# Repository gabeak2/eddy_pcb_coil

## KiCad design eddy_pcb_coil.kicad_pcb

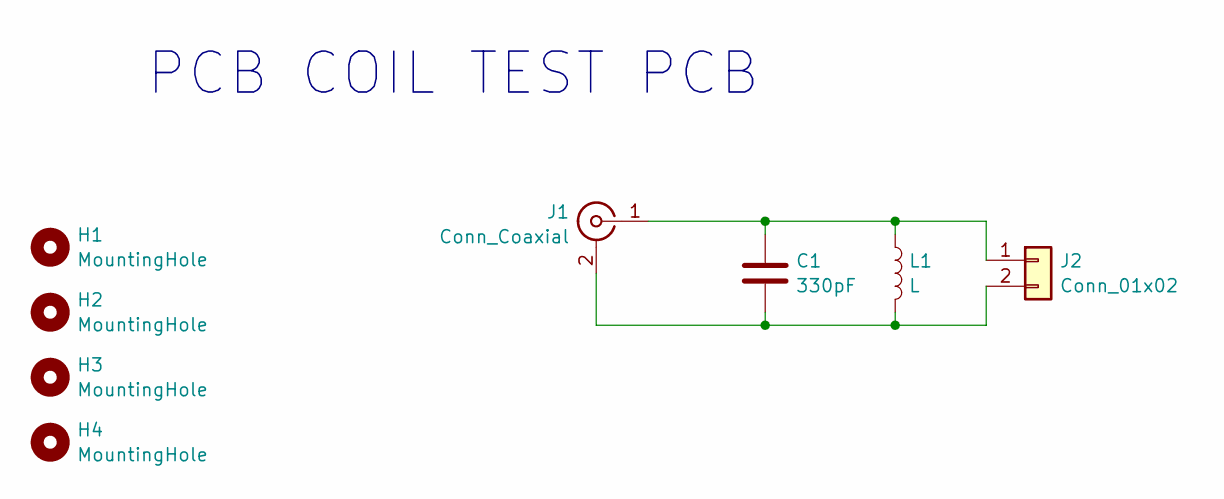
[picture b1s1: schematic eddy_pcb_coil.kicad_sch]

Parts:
C1: 330pF; C_0805_2012Metric; LCSC C527075
H1, H2, H3, H4: MountingHole; MountingHole_3.2mm_M3
J1: Conn_Coaxial; SMB_Jack_Vertical; LCSC C2797251
J2: Conn_01x02; PinHeader_1x02_P2.54mm_Vertical
L1: L; pcb_coil_30_turns_2_layers_30mm_od

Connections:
unnamed: C1.2, J1.2 (Ext), J2.2, L1.2
unnamed: C1.1, J1.1 (In), J2.1, L1.1

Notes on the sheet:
PCB COIL TEST PCB

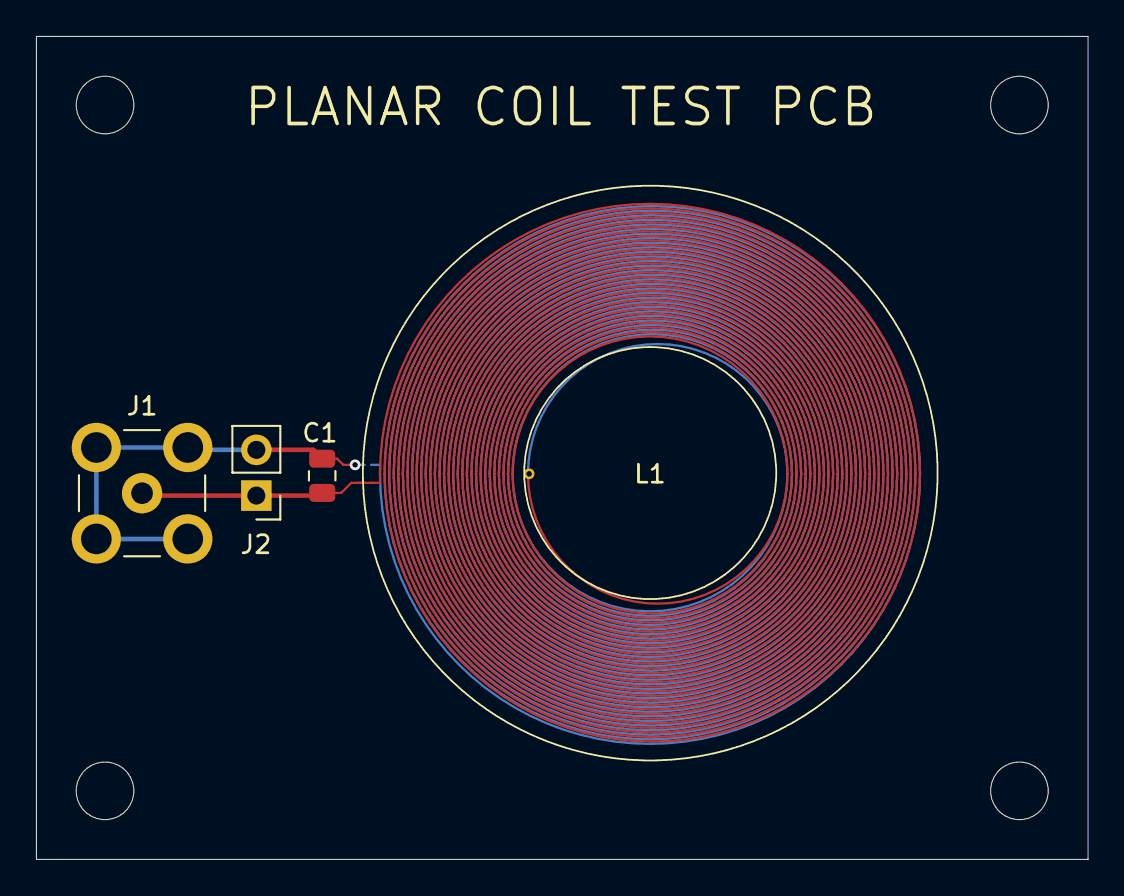
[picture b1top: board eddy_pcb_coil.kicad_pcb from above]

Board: 2 copper layers, 58.4 x 45.7 mm, 8 parts (0 on the bottom side), 2 nets.
